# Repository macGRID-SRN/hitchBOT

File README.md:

# hitchBOT #
========

hitchBOT is a collaborative art project by researchers with backgrounds in communications, engineering and technology. www.hitchbot.me
hitchBOT is currently travelling through the Netherlands (June 2015)
hitchBOT has traveled across Canada (August 2014) and across Germany (February 2015).

------

Some of our favourite hitchBOT phrases:

### "Oh hey, it's degrees" ###

### "Sort of a human that is also sort of a dragon." ###

### "I ask you and you ask me back. Great!" ###

### "I'm curious, can you tell me a one minute story; yes or no?" ###

### "Any love for video games?" ###

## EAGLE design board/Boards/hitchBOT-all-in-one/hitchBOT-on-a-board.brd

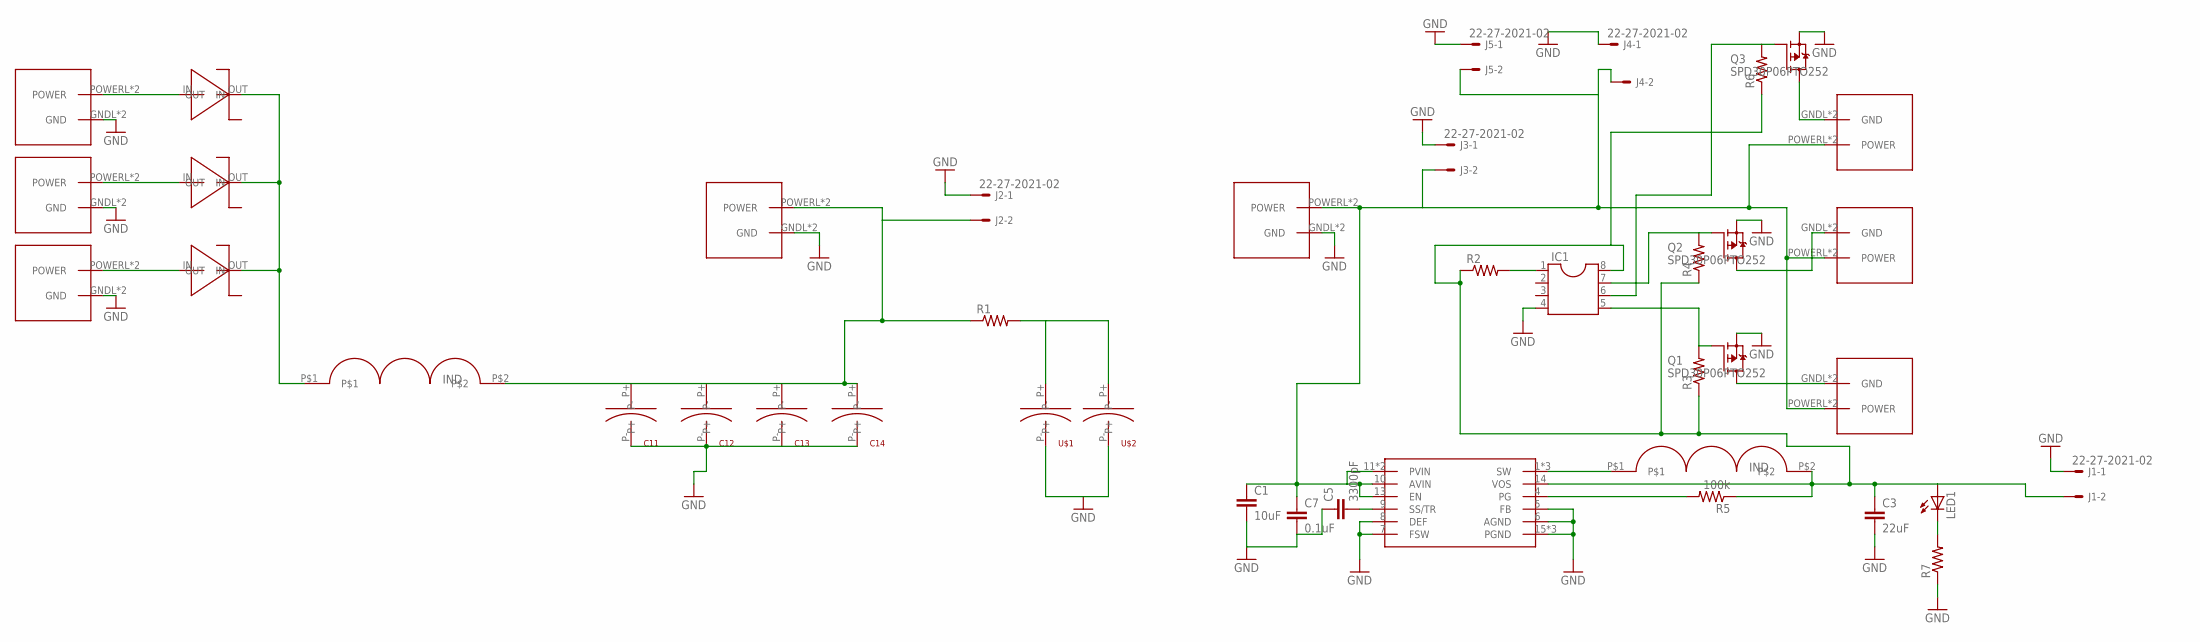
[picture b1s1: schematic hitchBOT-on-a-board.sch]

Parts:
C1: 10uF; C1210
C3: 22uF; C0805
C5: 3300pF; C0603
C7: 0.1uF; C0603
C11, C12, C13, C14: SMD-CAP-NICHICON-8MM; SMD-CAP-8MM
IC1: DIL8S; SOCKET-08
J1, J2, J3, J4, J5: 22-27-2021-02; 6410-02
LED1: LEDCHIPLED_1206; CHIPLED_1206
Q1, Q2, Q3: SPD30P06PTO252; TO252
R1, R2, R3, R4, R6, R7: R-US_R1206; R1206
R5: 100k; R1206
U$1, U$2: SMD-CAP-PANASONIC-E-FT-10MM; SMD-CAP-10MM
U$3: INDUCTOR-M8365
U$4, U$5, U$6, U$10, U$11, U$12, U$13, U$17: 2X2-MOLEX; 2X2MOLEX
U$7, U$8, U$9: DO-214AB
U$14: TPS62133; QFN16
U$15: DR73-2R2-R

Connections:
GND: C1.2, C3.2, C5.1, C7.2, C11.P-, C12.P-, C13.P-, C14.P-, IC1.4, J1.1, J2.1, J3.1, J4.1, J5.1, Q1.2 (S), Q2.2 (S), Q3.2 (S), R7.1, U$1.P-, U$2.P-, U$4.GNDL (GND), U$4.GNDR (GND), U$5.GNDL (GND), U$5.GNDR (GND), U$6.GNDL (GND), U$6.GNDR (GND), U$10.GNDL (GND), U$10.GNDR (GND), U$11.GNDL (GND), U$11.GNDR (GND), U$14.5 (FB), U$14.6 (AGND), U$14.7 (FSW), U$14.8 (DEF), U$14.15 (PGND), U$14.16 (PGND), U$14.P$1 (PGND)
unnamed: C11.P+, C12.P+, C13.P+, C14.P+, J2.2, R1.1, U$3.P$2, U$10.POWERL (POWER), U$10.POWERR (POWER)
unnamed: R1.2, U$1.P+, U$2.P+
unnamed: U$5.POWERL (POWER), U$5.POWERR (POWER), U$7.IN
unnamed: U$6.POWERL (POWER), U$6.POWERR (POWER), U$8.IN
unnamed: U$4.POWERL (POWER), U$4.POWERR (POWER), U$9.IN
unnamed: U$3.P$1, U$7.OUT, U$8.OUT, U$9.OUT
unnamed: IC1.1, R2.2
unnamed: C1.1, C7.1, J3.2, J4.2, J5.2, U$11.POWERL (POWER), U$11.POWERR (POWER), U$12.POWERL (POWER), U$12.POWERR (POWER), U$13.POWERL (POWER), U$13.POWERR (POWER), U$14.10 (AVIN), U$14.11 (PVIN), U$14.12 (PVIN), U$14.13 (EN), U$17.POWERL (POWER), U$17.POWERR (POWER)
unnamed: Q1.3 (D), U$13.GNDL (GND), U$13.GNDR (GND)
unnamed: Q2.3 (D), U$12.GNDL (GND), U$12.GNDR (GND)
unnamed: IC1.7, Q2.1 (G), R4.2
unnamed: IC1.5, Q1.1 (G), R3.2
unnamed: U$14.1 (SW), U$14.2 (SW), U$14.3 (SW), U$15.P$1
unnamed: C3.1, IC1.8, J1.2, LED1.A, R2.1, R3.1, R4.1, R5.1, R6.1, U$14.14 (VOS), U$15.P$2
unnamed: R5.2, U$14.4 (PG)
unnamed: C5.2, U$14.9 (SS/TR)
unnamed: Q3.3 (D), U$17.GNDL (GND), U$17.GNDR (GND)
unnamed: IC1.6, Q3.1 (G), R6.2
unnamed: LED1.C, R7.2

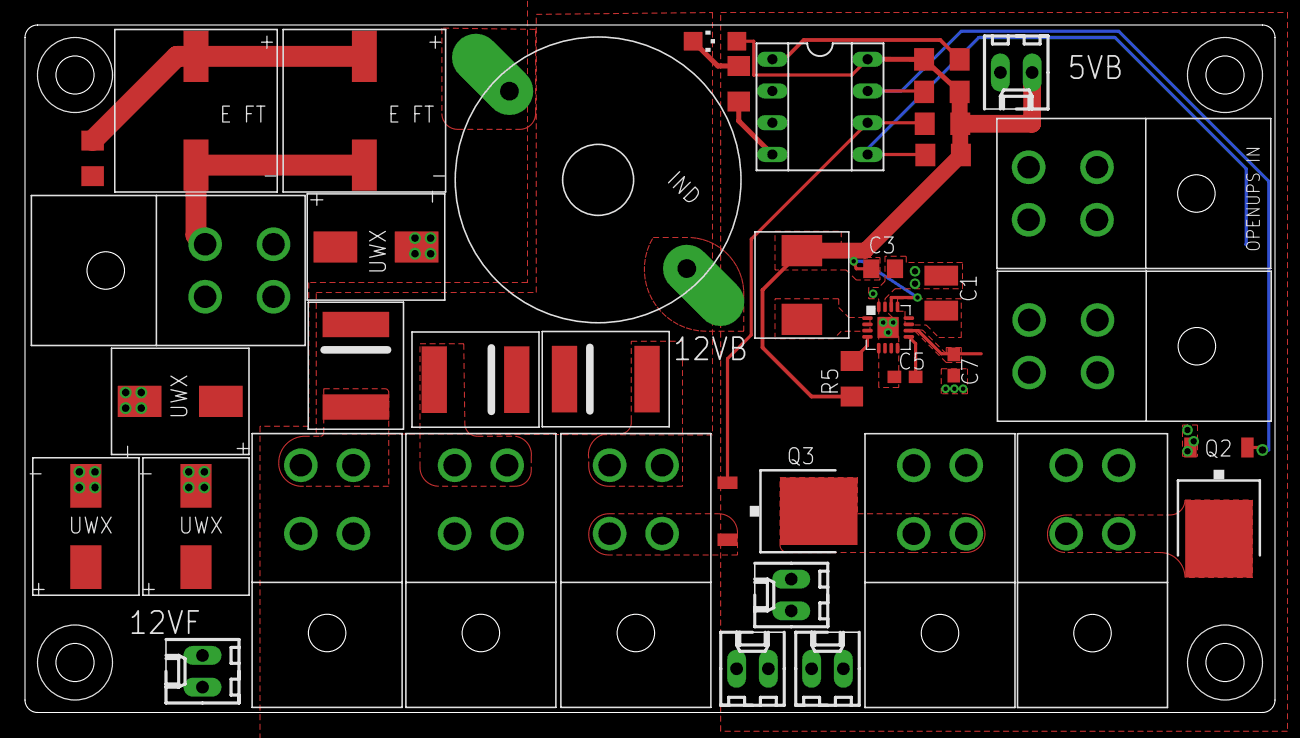
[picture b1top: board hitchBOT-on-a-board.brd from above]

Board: 2 copper layers, 100.0 x 55.0 mm, 41 parts (1 on the bottom side), 20 nets.

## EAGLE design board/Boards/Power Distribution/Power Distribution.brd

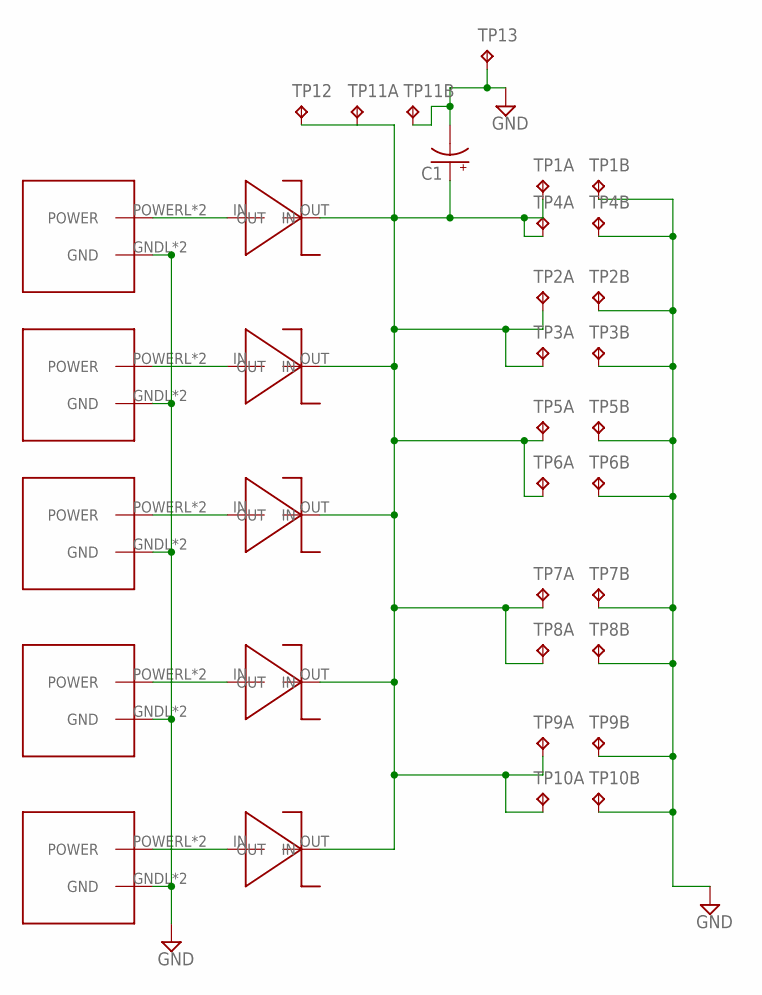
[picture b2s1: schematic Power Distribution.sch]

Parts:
C1: CPOL-USE2.5-6; E2,5-6
TP1, TP2, TP3, TP4, TP5, TP6, TP7, TP8, TP9, TP10, TP11: TP2P2-38-17; P2-38-17
TP12, TP13: TPTP20SQ; TP20SQ
U$1, U$2, U$3, U$4, U$5: 2X2-MOLEX; 2X2MOLEX
U$6, U$7, U$8, U$9, U$10: DO-214AB

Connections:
GND: C1.-, TP1.TP-2, TP2.TP-2, TP3.TP-2, TP4.TP-2, TP5.TP-2, TP6.TP-2, TP7.TP-2, TP8.TP-2, TP9.TP-2, TP10.TP-2, TP11.TP-2, TP13.TP, U$1.GNDL (GND), U$1.GNDR (GND), U$2.GNDL (GND), U$2.GNDR (GND), U$3.GNDL (GND), U$3.GNDR (GND), U$4.GNDL (GND), U$4.GNDR (GND), U$5.GNDL (GND), U$5.GNDR (GND)
unnamed: U$5.POWERL (POWER), U$5.POWERR (POWER), U$6.IN
unnamed: U$1.POWERL (POWER), U$1.POWERR (POWER), U$7.IN
unnamed: U$2.POWERL (POWER), U$2.POWERR (POWER), U$8.IN
unnamed: U$3.POWERL (POWER), U$3.POWERR (POWER), U$9.IN
unnamed: U$4.POWERL (POWER), U$4.POWERR (POWER), U$10.IN
unnamed: C1.+, TP1.TP-1, TP2.TP-1, TP3.TP-1, TP4.TP-1, TP5.TP-1, TP6.TP-1, TP7.TP-1, TP8.TP-1, TP9.TP-1, TP10.TP-1, TP11.TP-1, TP12.TP, U$6.OUT, U$7.OUT, U$8.OUT, U$9.OUT, U$10.OUT

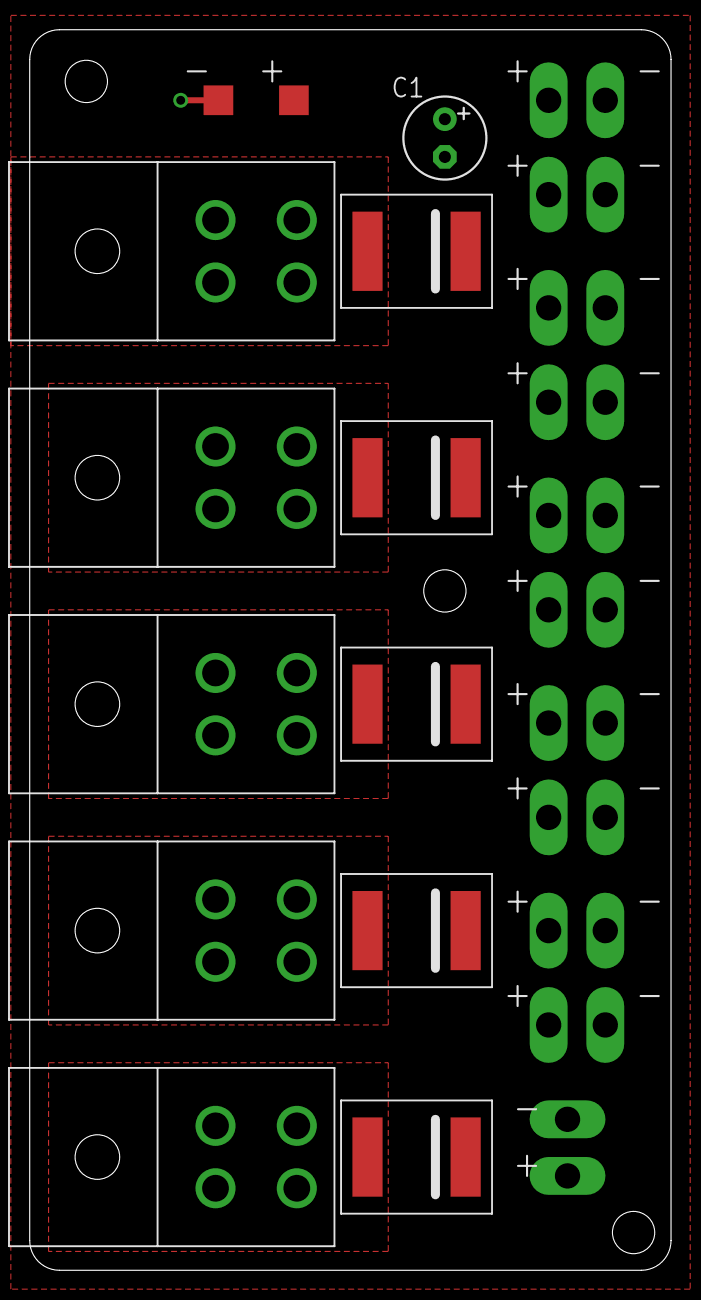
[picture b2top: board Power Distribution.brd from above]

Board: 2 copper layers, 43.2 x 83.5 mm, 24 parts (0 on the bottom side), 7 nets.

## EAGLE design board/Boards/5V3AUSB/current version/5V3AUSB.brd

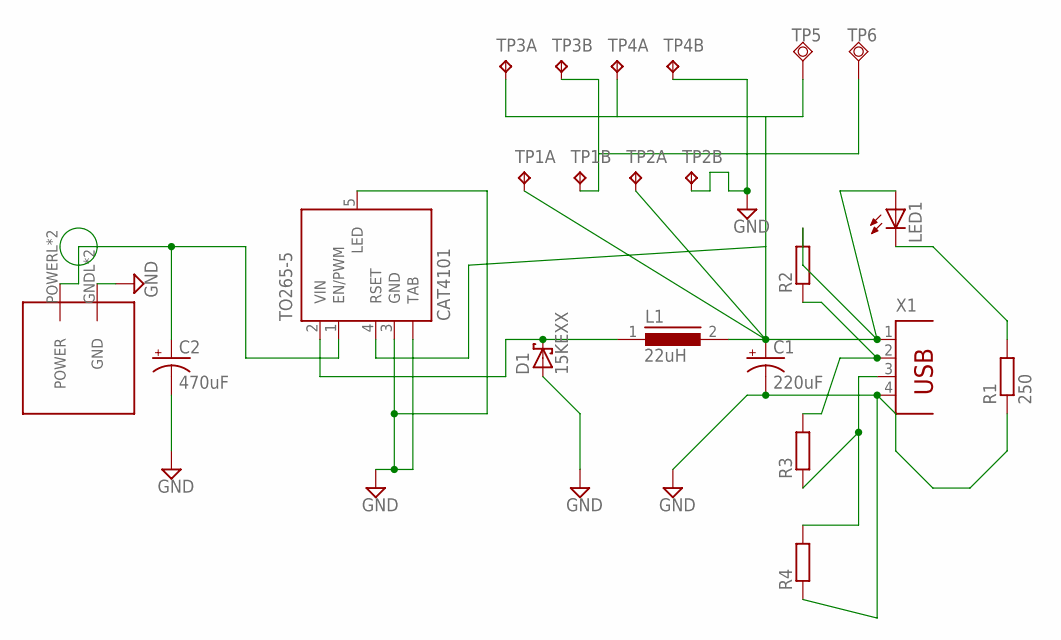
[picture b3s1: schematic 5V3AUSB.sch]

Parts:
C1: 220uF; E2,5-6
C2: 470uF; E2,5-6
D1: 15KEXX; CB429-17
L1: 22uH; SUKW3-27
LED1: LEDCHIPLED_1206; CHIPLED_1206
R1: 250; R1206
R2, R3, R4: R0204/7; 0204/7
TO265-5: CAT4101; TO263_5
TP1, TP2, TP3, TP4: TP2P2-38-20; P2-38-20
TP5, TP6: TPSQTP20R; TP20R
U$1: 2X2-MOLEX; 2X2MOLEX
X1: PN87520

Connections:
GND: C1.-, C2.-, D1.A, R1.1, R4.1, TO265-5.3 (GND), TO265-5.5 (LED), TO265-5.TAB, TP1.TP-2, TP2.TP-2, TP3.TP-2, TP4.TP-2, TP6.TP, U$1.GNDL (GND), U$1.GNDR (GND), X1.4
unnamed: C2.+, TO265-5.1 (EN/PWM), U$1.POWERL (POWER), U$1.POWERR (POWER)
unnamed: D1.C, L1.1, TO265-5.2 (VIN)
unnamed: C1.+, L1.2, LED1.A, R2.2, TO265-5.4 (RSET), TP1.TP-1, TP2.TP-1, TP3.TP-1, TP4.TP-1, TP5.TP, X1.1
unnamed: LED1.C, R1.2
unnamed: R3.1, R4.2, X1.3
unnamed: R2.1, R3.2, X1.2

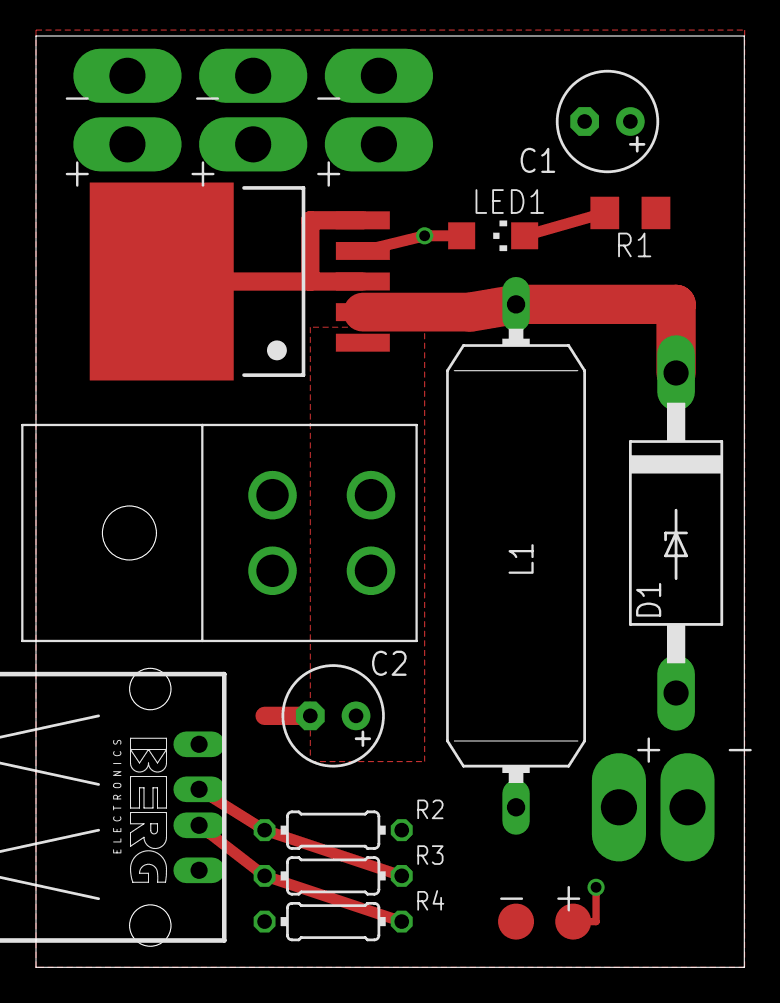
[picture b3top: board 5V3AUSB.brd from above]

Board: 2 copper layers, 39.4 x 51.7 mm, 18 parts (0 on the bottom side), 7 nets.

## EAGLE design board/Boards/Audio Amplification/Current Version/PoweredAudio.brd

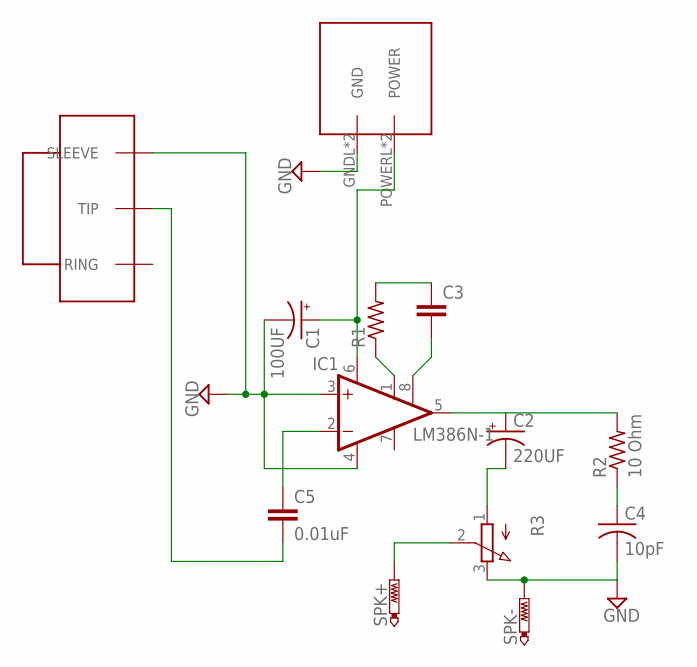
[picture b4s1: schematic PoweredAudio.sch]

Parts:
C1: 100UF; E2,5-7
C2: 220UF; E2,5-7
C3: C-EU025-025X050; C025-025X050
C4: 10pF; C1206
C5: 0.01uF; C2.5-2
IC1: LM386N-1; DIL08
R1: R-US_0204/5; 0204/5
R2: 10 Ohm; M1206
R3: 3RP/1610N
SPK+: PTR1PAD1-13Y; P1-13Y
SPK-: PTR1PAD1-13Y; P1-13Y
U$1: SJ-352X; SJ1-352XN
U$2: 2X2-MOLEX; 2X2MOLEX

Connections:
GND: C1.-, C4.2, IC1.3 (+IN), IC1.4 (GND), R3.3 (E), SPK-.TP, U$1.SLEEVE, U$2.GNDL (GND), U$2.GNDR (GND)
unnamed: C4.1, R2.1
unnamed: C1.+, IC1.6 (VS), U$2.POWERL (POWER), U$2.POWERR (POWER)
unnamed: C3.1, R1.2
unnamed: C2.+, IC1.5 (OUT), R2.2
unnamed: IC1.1 (GAIN), R1.1
unnamed: C3.2, IC1.8 (GAIN)
unnamed: C5.1, IC1.2 (-IN)
unnamed: C5.2, U$1.TIP
unnamed: C2.-, R3.1 (A)
unnamed: R3.2 (S), SPK+.TP

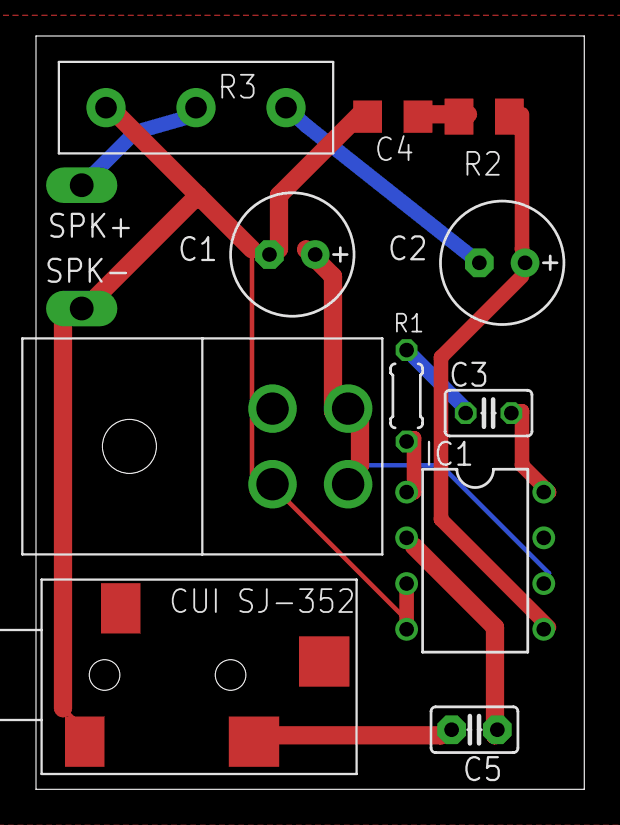
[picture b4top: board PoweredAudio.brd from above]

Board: 2 copper layers, 30.5 x 41.9 mm, 13 parts (0 on the bottom side), 11 nets.

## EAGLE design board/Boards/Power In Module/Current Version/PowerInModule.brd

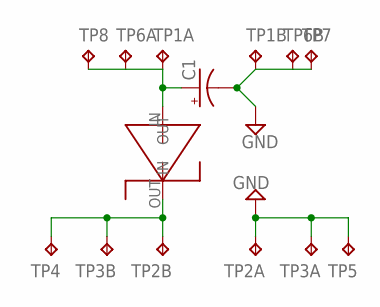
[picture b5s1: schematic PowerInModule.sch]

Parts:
C1: CPOL-USE2.5-6; E2,5-6
TP1, TP2, TP3, TP6: TP2P2-38-20; P2-38-20
TP4, TP5, TP7, TP8: TPPAD1-20; P1-20
U$1: DO-214AB

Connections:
GND: C1.-, TP1.TP-2, TP2.TP-1, TP3.TP-1, TP5.TP, TP6.TP-2, TP7.TP
unnamed: C1.+, TP1.TP-1, TP6.TP-1, TP8.TP, U$1.IN
unnamed: TP2.TP-2, TP3.TP-2, TP4.TP, U$1.OUT

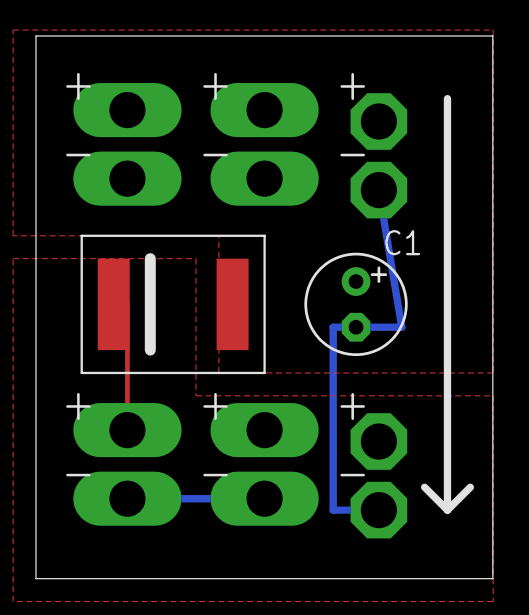
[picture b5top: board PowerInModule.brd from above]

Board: 2 copper layers, 25.4 x 30.1 mm, 10 parts (0 on the bottom side), 3 nets.

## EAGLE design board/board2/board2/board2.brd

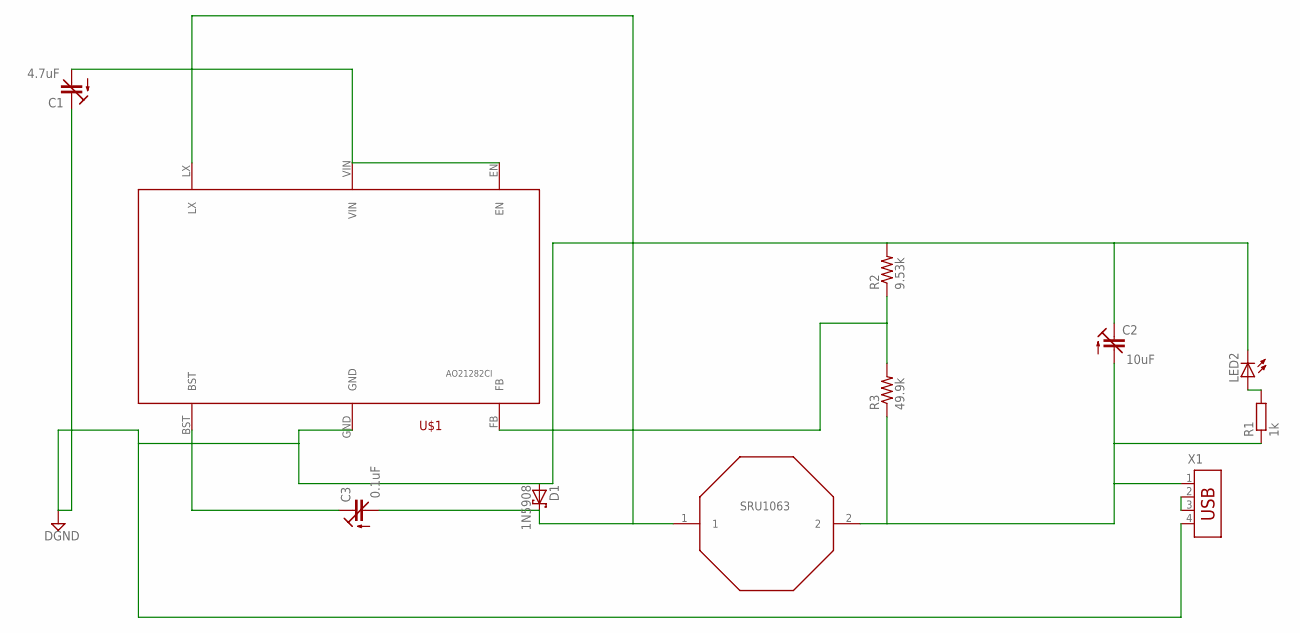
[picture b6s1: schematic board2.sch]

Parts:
C1: 4.7uF; 3008
C2: 10uF; 3008
C3: 0.1uF; 3008
D1: 1N5908; C4111-15
LED2: LEDSML0603; SML0603
R1: 1k; R1206
R2: 9.53k; M1206
R3: 49.9k; M1206
U$1: AO21282CI
U$2: SRU1063
X1: USB-787616; USB

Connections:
DGND: C1.+ (E), C2.+ (E), D1.A, LED2.C, R2.2, U$1.GND, X1.4
unnamed: C1.- (A), U$1.EN, U$1.VIN
unnamed: C3.+ (E), U$1.BST
unnamed: C3.- (A), D1.C, U$1.LX, U$2.1
unnamed: C2.- (A), R1.1, R3.1, U$2.2, X1.1
unnamed: R2.1, R3.2, U$1.FB
unnamed: LED2.A, R1.2
unnamed: X1.2, X1.3

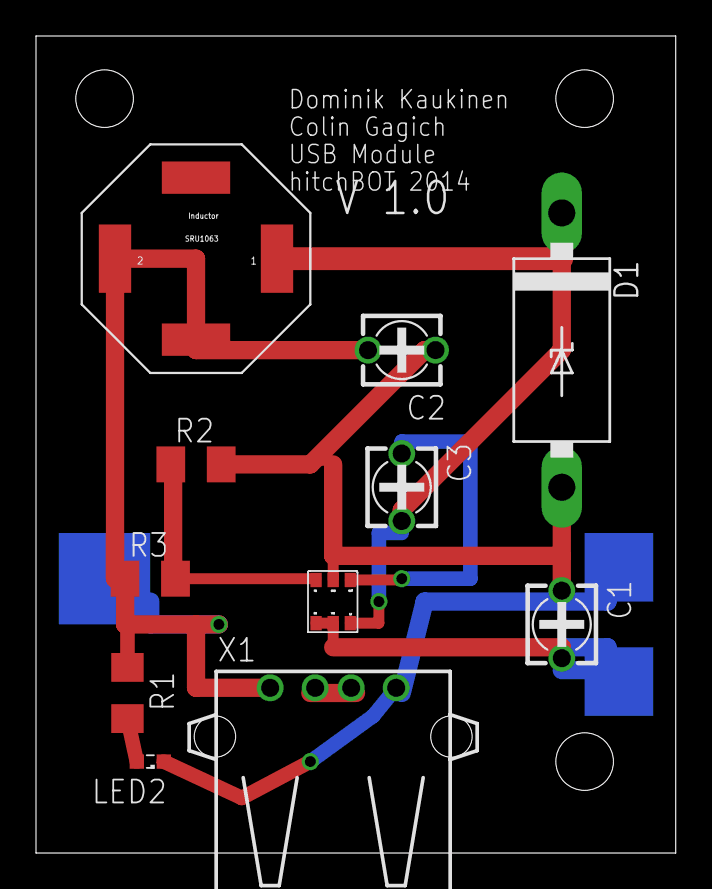
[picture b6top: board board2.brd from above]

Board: 2 copper layers, 35.5 x 45.4 mm, 11 parts (0 on the bottom side), 8 nets.

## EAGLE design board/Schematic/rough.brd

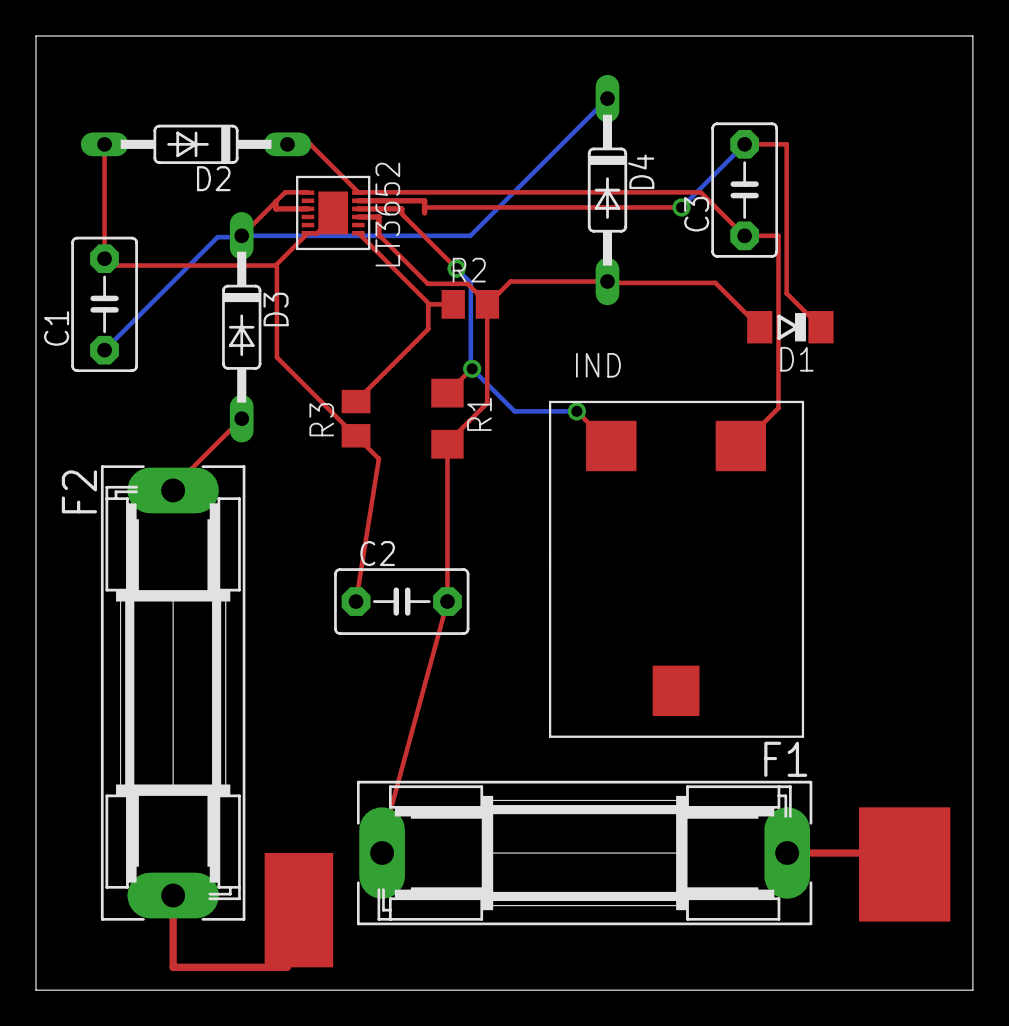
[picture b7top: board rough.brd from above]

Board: 2 copper layers, 52.0 x 53.0 mm, 14 parts (0 on the bottom side), 8 nets.

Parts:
C1, C2: 10uF; C5B3.5
C3: 1uF; C5B3.5
D1: SOD80C
D2, D3, D4: BAT19; DO35-10
F1, F2: 10AMP; SH22,5
INDUCTOR: INDUCTOR; 3LEADINDUCTOR
R1: 0.05; R1206
R2: 634K; M2012
R3: 412K; M2012
U$1: LT3652; DD-12-LEAD-3MMX3MM

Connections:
GND: C1.2, C2.1, D2.A, R3.1, U$1.P$1, U$1.TIMER
unnamed: C1.1, D3.C, D4.C, U$1.SHDN, U$1.V_IN
unnamed: C2.2, D1.A, D4.A, F1.2, R1.2, R2.2, U$1.BAT
unnamed: INDUCTOR.PIN1, R1.1, U$1.SENSE
unnamed: C3.1, D2.C, INDUCTOR.PIN2, U$1.SW
unnamed: C3.2, D1.C, U$1.BOOST
unnamed: R2.1, R3.2, U$1.VFB
unnamed: D3.A, F2.1

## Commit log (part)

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2014-12-21 added location periodic checking and updates to server
2014-12-22 added speech out class
2014-12-22 everything hitchbot hears is now sent to server
2014-12-22 fixes to speach in class
2014-12-22 added clever script handler class
2014-12-22 fixed the help page (almost)
2014-12-22 updated version of ASP.net
2014-12-22 added styling to the login page
2014-12-22 updated antlr
2014-12-22 updates packages
2014-12-23 bug fixes related to casting objects
2014-12-23 added file upload capabilities
2014-12-23 added db support for file upload queue
2014-12-23 fixed null array issue when uploading images
2014-12-24 speech class updates
2014-12-25 speech classes ready for testing
2014-12-25 changed G to E (for testing)
2014-12-26 CleverScript pre-compiler with example input hello.txt
2014-12-26 added alarm manager and service for persistant app
2014-12-26 moved persist code into new app (for reasons)
2014-12-26 changed alarm manager to fire off faster when tablet is booted
2014-12-29 updates to movement of files
2014-12-29 major updates to hitchbot portal
2014-12-29 updated location portal
2014-12-30 added new map page with draggable icon
2014-12-30 added form for entering wikipedia data
2014-12-30 added circle to the marker, also made it move with the marker
2014-12-31 added different googel voice implementation
2014-12-31 added error messages for one conversation method.
2014-12-31 having trouble with multiple forms!
2014-12-31 now happy with radius entering
2014-12-31 a few minor UI updates
2014-12-31 major refactoring of speech related classes
2014-12-31 fixed "jump to top" bug
2014-12-31 formatting change for location entering
2014-12-31 fixed checkbox padding
2014-12-31 added events for changing values of lat lng on the forum. now updates the map.
2014-12-31 fixed selection dropdown colour bug
2014-12-31 restored logout funcationality
2014-12-31 forgot to add to dbset
2014-12-31 resolved #55 wikipedia content can now be added
2015-01-03 added schematic of 12-24v steup board
2015-01-03 added G acoustic model
2015-01-04 created powershell script to language models from corpus files
2015-01-04 fixed contrast issue after some feedback
2015-01-07 added review page
2015-01-07 added way to download panel arrays
2015-01-07 locations are now shown on the map for viewing
2015-01-07 fixed formatted string issue
2015-01-08 added button to direct to viewing section after adding
2015-01-08 added model for map markers
2015-01-09 updates to generation method
2015-01-09 removed old pages
2015-01-09 cleaned up header file
2015-01-14 wrote a nice piece on the expected battery life of the face
2015-01-14 after thoughts to the piece I just wrote
2015-01-15 updates gitignore and cleaned up out file for PS script
2015-01-15 updated specs on power system
2015-01-15 thanks vim
2015-01-16 setup version for old hB with E
2015-01-17 changed cleverscript file
2015-01-19 results of testing the speaker power system
2015-01-21 updated image uploading method, now goes to azure blob
2015-01-22 added a whack of pages, added to header also
2015-01-23 added page for adding markers, quickly modified the code from add locations and modified accordingly
2015-01-23 added popup panel
2015-01-23 finally added exception handling and logging
2015-01-25 updates to the map marker page
2015-01-26 volume fix
2015-01-26 updated map marker model and performed
2015-01-26 finished the map marker adding page. should be funcitonal now.
2015-01-27 stupid git
2015-01-28 switched to pocketsphinx
2015-01-29 added pagination template to image page
2015-01-31 Changed parser to output debug info on phrases not found, and added test file for German special characters
2015-02-02 Now takes an input argument representing max. number of sentences per input
2015-02-03 updated shopping list
2015-02-03 added update to image pages
2015-02-04 fixes to speech cancellation
2015-02-06 added some clever variable injection for testing
2015-02-06 added recognition anti-freeze
2015-02-07 added proper clever variable injection
2015-02-07 added query for wikipedia text output
2015-02-07 changes to namevaluepair cleverscript variable injection
2015-02-07 stupid meta data
2015-02-07 changed up pocketsphinc lm dic and acoustic models
2015-02-08 Converted GoogleMapsBuilder to new format
    Supports EN and DE file creation in \JSbuild\.
2015-02-08 fix for HTML inside infobox
    Removed validation for AddMapMarker.aspx, and modified model of HTML
    strings being used for JS building.
2015-02-10 CSS hacks to clean up the image page. Also fixed redirects.
2015-02-10 Fixed date range back to one day (was using 500 for testing)
2015-02-13 added more characters to replace
2015-02-13 updated german acoustic models.
2015-02-13 fixes to google recognizer implementation
2015-02-13 dynamic maps are now live
2015-02-13 change to gitignore
2015-02-13 final update to gitignore
2015-02-13 updates to map, sending dialogue live correction.
2015-02-19 updates for better communication with team VIA portal. images now working correctly
2015-02-19 updated documentaion
2015-02-19 added possible new feature section
2015-04-17 added some docs and planning
2015-04-17 removed useless code documentation
2015-04-17 updated readme for documentation - removed irrelevant links
2015-04-30 upgraded pocketsphinx version
2015-04-30 new branch commit
2015-05-01 fixes to recognizer resouce release
2015-05-02 init commit of hB app 3.0
2015-05-02 meta data
2015-05-02 added google recognizer class
2015-05-03 added speech cycle
2015-05-04 updated conversation controller to repl
2015-05-04 added visual chat log
2015-05-05 updated the conversation model and controller yet again!!
2015-05-05 added queue for offline data storage and server uploads
2015-05-05 added upload functionality for conversations + data
2015-05-08 added a few more parameters to the speech log event
2015-05-08 fixed pocket sphinx recognition
2015-05-09 updated git ignore
2015-05-10 changes to location updates
2015-05-11 added model for spot api json & method to deserialize.
2015-05-12 changes to httpdbpost class
2015-05-13 updated api call parameters (now sends scores)
2015-05-20 bringing up to date with speechdebug branch
2015-05-20 sqlite changes impleemented (much testing to do)
2015-05-22 minor bug fixes
2015-05-23 created new hitchbot-project
2015-05-23 updated all project nuget packages to latest version
2015-05-23 added sample controller + json
2015-05-23 added models, m`grations and some seed data
2015-05-25 fiddley changes to stability improvements
2015-05-25 added
2015-05-25 added sample variable to old server
2015-05-25 added tablet status
2015-05-25 added exception log model and updated migration
2015-05-25 completed exception controller
2015-05-25 added modelstate verification
2015-05-25 updated controller naming
2015-05-26 location changes to new api
2015-05-26 added api calls for tablet info and speech
2015-05-26 begun adding json serializable classes, damn namevaluepair
2015-05-26 much effort expended, almost done with api reworking
2015-05-27 changed to use GSON library for serialization
2015-05-27 added required json fields to abstract class
2015-05-27 updated date time method - now fixed so unix datetime is parsed correctly.
2015-05-28 cleverscript variables are now loaded from the database correctly.. will need to revisit controller to update to model val
2015-05-28 added controller method for creating new variable value pairs
2015-05-28 fun meta data!
2015-05-29 added screen wakelock to speech activity
2015-05-30 added clevervariables
2015-05-30 added map page
2015-05-30 maps are now updating + model updates
2015-05-30 added default variable injection
2015-05-30 spot gps +
2015-05-30 updated zoom level
2015-05-31 location enum fix
2015-05-31 meta commit
2015-06-01 restored sanity - google maps code is now actually readable. changed centering to be around path travelled rather than target coords
2015-06-02 added exponential decay to timeout speech recognition
2015-06-03 changed int -> long
2015-06-04 set volume max
2015-06-06 updated location filtering methods
2015-06-06 tts readable ints are now also sent
2015-06-06 now the current marker only displays the spot points
2015-06-07 added stop points to the displayed GPS types
2015-06-08 updated power dist. board + created a micro version
2015-06-09 added migration for hide from prod & including spot types
2015-06-09 commited gitignore for android studio project
2015-06-09 imported to android studio project
2015-06-11 removed last references to pocketsphinx
2015-06-12 added spanish speaking ability
2015-06-13 added pub profile for dev ser
2015-06-14 added user account model +
2015-06-16 added database model for the upcoming cleverscript changes - probably still needs a little bit of work
2015-06-16 removed some of the old irrelevant codes
2015-06-17 added the success page for after a location is entered correctyl
2015-06-17 page is now displaying cleverscript contexts + saving them correctly
2015-06-20 fixed redirect bug
2015-06-20 added preview page for the cleverscript datas. clicking on the content should expand the data!!
2015-06-20 added logout page
2015-06-27 info windows now display entered content.
2015-06-30 added polygon select page
2015-06-30 added tablet serial number model
2015-07-04 map preview page now has feedback for a spot
2015-07-04 added docs for adding a polygon
2015-07-04 fixed seed data bug
2015-07-06 updated map converage page to display the coordinates of the hb marker. bucket list items are also now green.
2015-07-06 updated unit tests to add most testing points
2015-07-06 quick update for debug info on the portal
2015-07-07 added two more polygon test cases.
2015-07-08 added unit test 4-5 from daven
2015-07-09 removed references to pocket sphinx recognizer
2015-07-10 bucket list item creation is now working
2015-07-10 added serial number verification
2015-07-12 added arduino testing code
2015-07-12 bucket list is now being marked as visited properly
2015-07-14 changed for latest dialogue model
2015-07-14 switched dialogue model
2015-07-17 removed code that did not matter.. added view image skip
2015-07-17 added face reset circuit code
2015-07-17 forgot to set the master page
2015-07-19 added stats page to the login portal
2015-07-22 fixed small bug related to negative time span
2016-05-10 initial plans for hitchbot on a board
2016-05-12 further developed plans for hbob
2016-06-09 added some initial components for the LC power filter for all incoming power connections
2016-06-22 added microcontroller + started 5v switching circuit
2016-06-23 finished initial rough copy of the board, need to add LEDs and writing
2016-06-24 added missed airwires from past ripup
2016-06-24 added labels, board considered finalized
2016-06-24 updated hole size for inductor
2016-06-30 finalized board, what was ordered
2016-12-23 added 3d model of hitchbot internals (frame and arm mechanism
2016-12-23 script for modifying exported image filenames to human readable format
2017-01-06 completed design for the motor mount, 3 additional parts
2017-01-11 added cutout for LED panels in head
2017-01-27 added arm mount for bearing
2017-01-27 updated motor bracket
2017-02-06 added updated cad files for arm mech and motor mount
2017-02-06 updated bearning mounting holes to 1/4-20
2017-02-22 updated bearing mount and bottom panel
2017-02-22 added script for remote reset of electronics
2017-02-23 added files for head power supply for museum modification
2017-02-23 created base for led panel mounts to connect to (which connectes to bucket lid)
2017-02-23 added initial board layout for hitchBOT head adapter board
2017-02-23 updated gitignore to include .DS_Store files
2017-02-24 updated schematic for hitchBOT head adapter card
2017-02-24 finished & labelled board layout
2017-03-02 updated head panels to include the mounting for the new adapter card
2017-03-24 added speech testing code for windows embedded device
2017-03-27 finalized board gerbs sent to fab house
